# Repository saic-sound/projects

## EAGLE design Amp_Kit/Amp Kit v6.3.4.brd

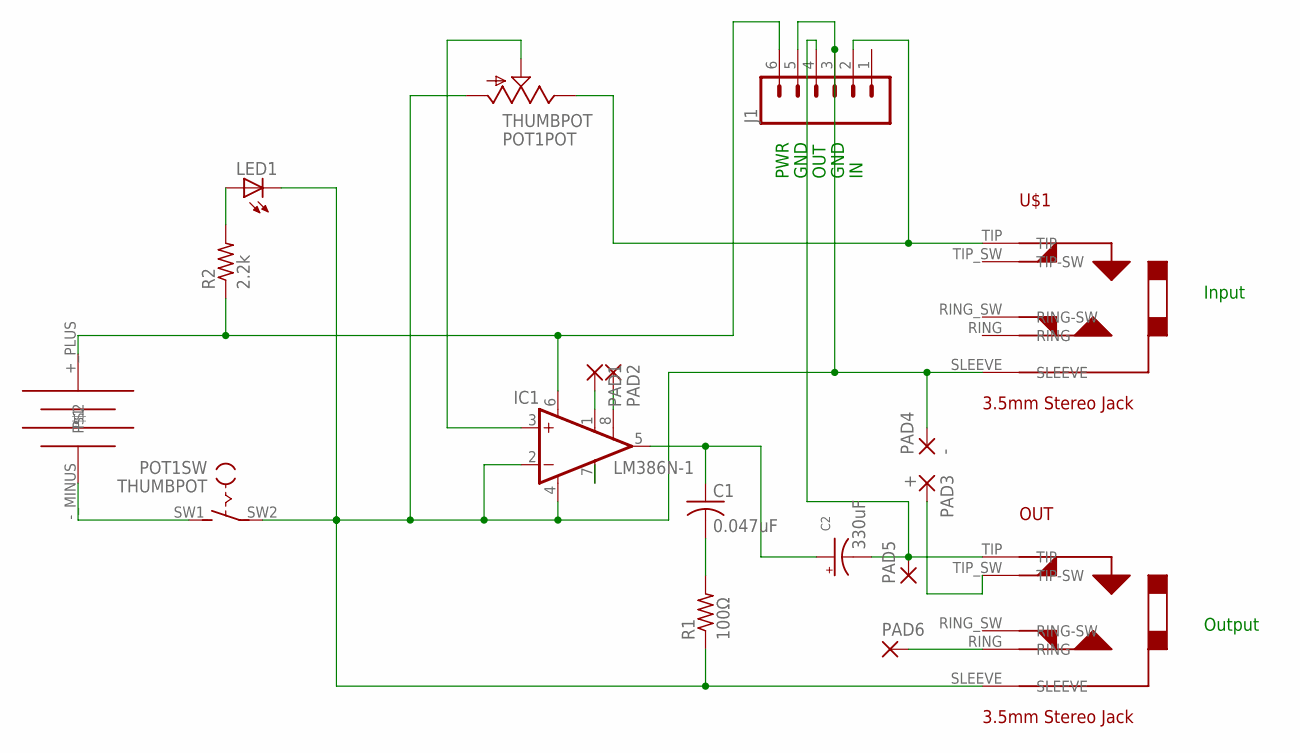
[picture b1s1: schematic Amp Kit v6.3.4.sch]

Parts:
C1: 0.047uF; C050-024X044
C2: 330uF; E1,8-4
IC1: LM386N-1; DIL08
J1: CONN_06NO_SILK_FEMALE_PTH; 1X06_NO_SILK
LED1: LED5MM
OUT: CUI_STEREO_JACK
PAD1, PAD2, PAD5, PAD6: SMD2; SMD1,27-2,54
PAD3: +; 4,16O1,6
PAD4: -; 4,16O1,6
POT1: THUMBPOT; THUMBWHEEL
R1: 100Ω; 0207/7
R2: 2.2k; 0207/7
U$1: CUI_STEREO_JACK
U$2: 9V_BATCLIP_AMP2

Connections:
unnamed: IC1.2 (-IN), IC1.4 (GND), J1.3, J1.5, LED1.K (C), OUT.SLEEVE, PAD4.1, POT1.1 (A), POT1.SW2, R1.1, U$1.SLEEVE
unnamed: OUT.TIP_SW (TIP-SW), PAD3.1
unnamed: C1.1, C2.+, IC1.5 (OUT)
unnamed: IC1.3 (+IN), POT1.2 (S)
unnamed: IC1.1 (GAIN), PAD1.1
unnamed: C2.-, J1.4, OUT.TIP, PAD5.1
unnamed: J1.2, POT1.3 (E), U$1.TIP
unnamed: LED1.A, R2.2
unnamed: POT1.SW1 (S), U$2.-_MINUS
unnamed: IC1.8 (GAIN), PAD2.1
unnamed: C1.2, R1.2
unnamed: OUT.RING, PAD6.1
unnamed: IC1.6 (VS), J1.6, R2.1, U$2.+_PLUS

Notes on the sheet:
Output
Input
PWR
GND
OUT

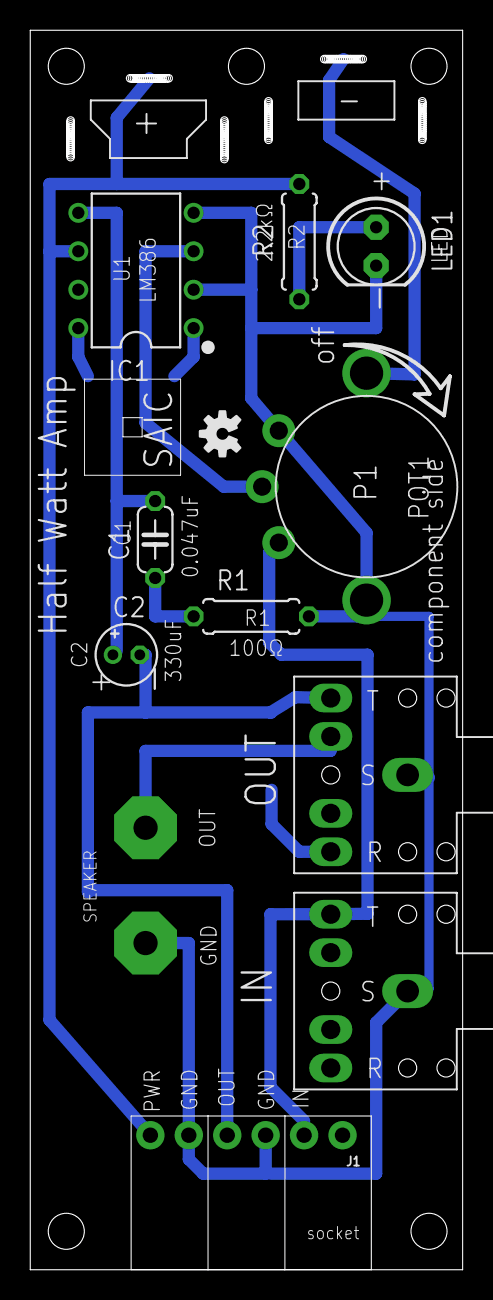
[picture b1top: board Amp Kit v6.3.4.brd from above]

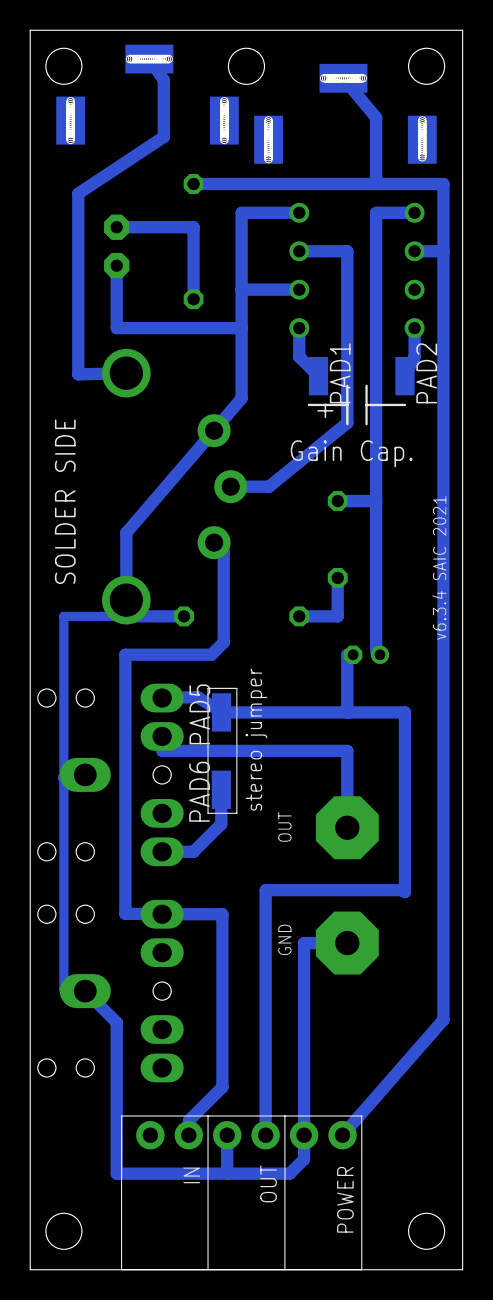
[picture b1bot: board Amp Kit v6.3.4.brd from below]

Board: 2 copper layers, 28.6 x 81.9 mm, 18 parts (4 on the bottom side), 13 nets.

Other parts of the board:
U$4: OSHW-LOGO-S

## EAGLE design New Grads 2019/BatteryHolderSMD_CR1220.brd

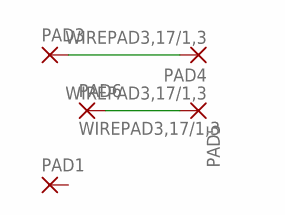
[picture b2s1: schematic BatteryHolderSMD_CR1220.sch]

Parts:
PAD1, PAD3: SMD5; SMD2,54-5,08
PAD4, PAD5, PAD6: WIREPAD3,17/1,3; 3,17/1,3

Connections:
unnamed: PAD3.1, PAD4.1
unnamed: PAD5.1, PAD6.1

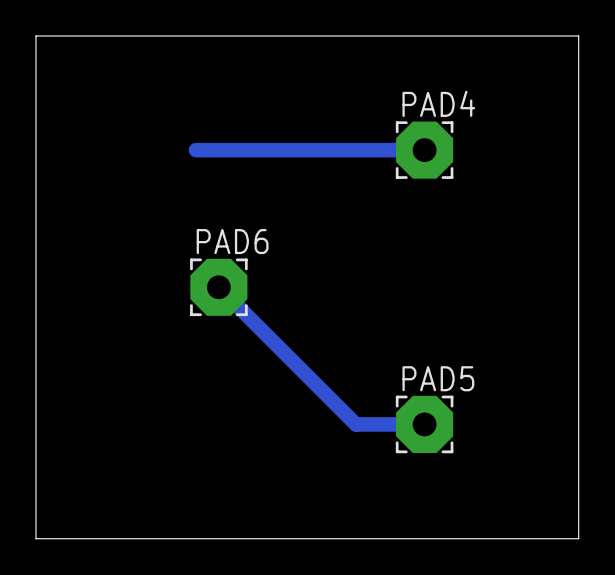
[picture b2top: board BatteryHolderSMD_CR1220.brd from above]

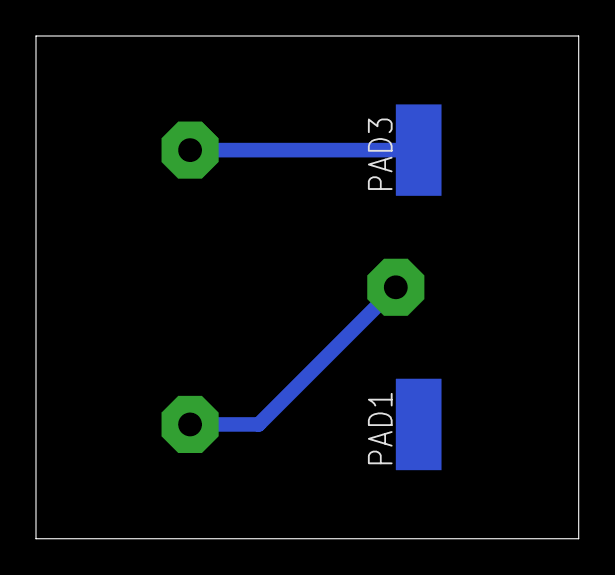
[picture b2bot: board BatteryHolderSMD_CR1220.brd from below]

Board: 2 copper layers, 30.1 x 27.9 mm, 5 parts (2 on the bottom side), 2 nets.

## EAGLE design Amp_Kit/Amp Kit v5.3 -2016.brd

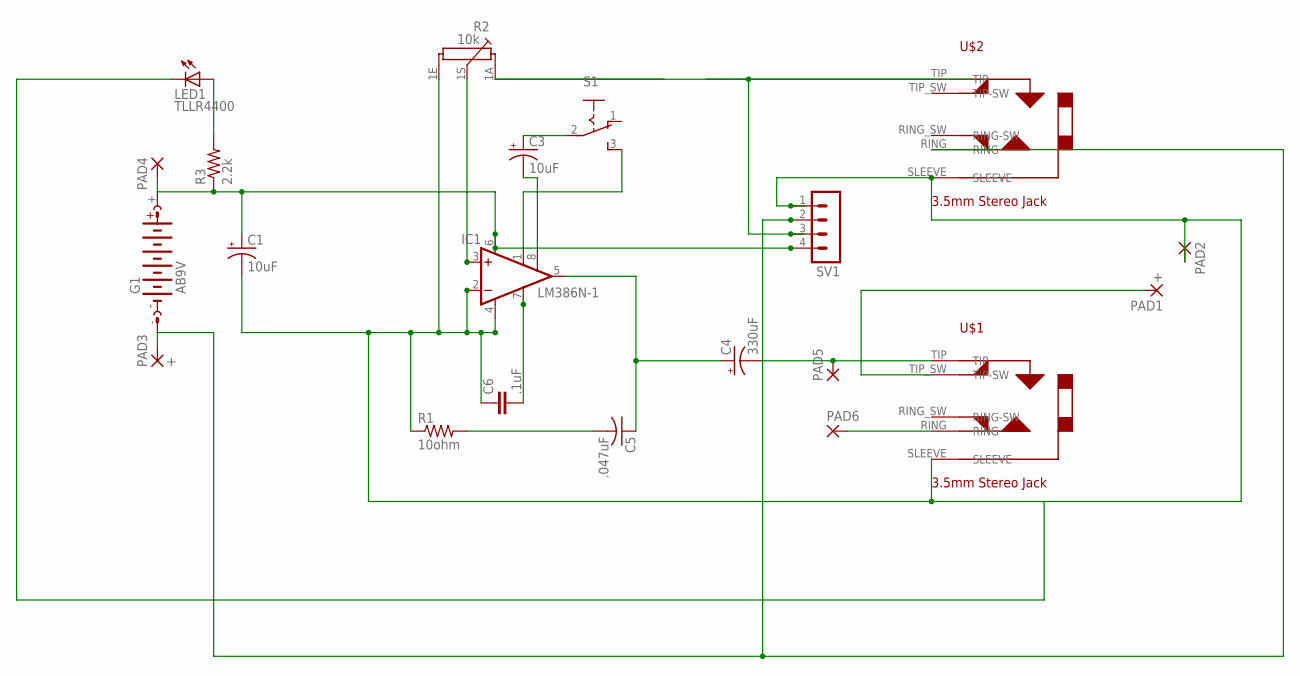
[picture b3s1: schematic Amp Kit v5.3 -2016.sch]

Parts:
C1, C3: 10uF; E2-5
C4: 330uF; E3,5-8
C5: .047uF; C050-025X075
C6: .1uF; C050-035X075
G1: AB9V
IC1: LM386N-1; DIL08
LED1: TLLR4400; LED3MM
PAD1, PAD3: +; 3,81/1,4
PAD2, PAD4: 3,81/1,4
PAD5, PAD6: SMD2; SMD1,27-2,54
R1: 10ohm; 0207/7
R2: 10k; PC16S
R3: 2.2k; 0207/7
S1: 255SB
SV1: MA04-1
U$1, U$2: PICAXE_STEREOJACKSOCKET

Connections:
unnamed: C5.2, R1.2
unnamed: R2.1A, SV1.3, U$2.TIP
unnamed: C4.+, C5.1, IC1.5 (OUT)
unnamed: IC1.3 (+IN), R2.1S
unnamed: C1.+, G1.+, IC1.6 (VS), PAD4.1, R3.1, SV1.4
unnamed: C4.-, PAD5.1, U$1.TIP
unnamed: C6.2, IC1.7 (BYPASS)
unnamed: C3.+, S1.2
unnamed: LED1.A, R3.2
unnamed: IC1.1 (GAIN), S1.3 (S)
unnamed: C1.-, C6.1, IC1.2 (-IN), IC1.4 (GND), LED1.K (C), PAD2.1, R1.1, R2.1E, SV1.1, U$1.SLEEVE, U$2.SLEEVE
unnamed: G1.-, PAD3.1, SV1.2, U$2.RING
unnamed: PAD6.1, U$1.RING
unnamed: C3.-, IC1.8 (GAIN)
unnamed: PAD1.1, U$1.TIP_SW (TIP-SW)

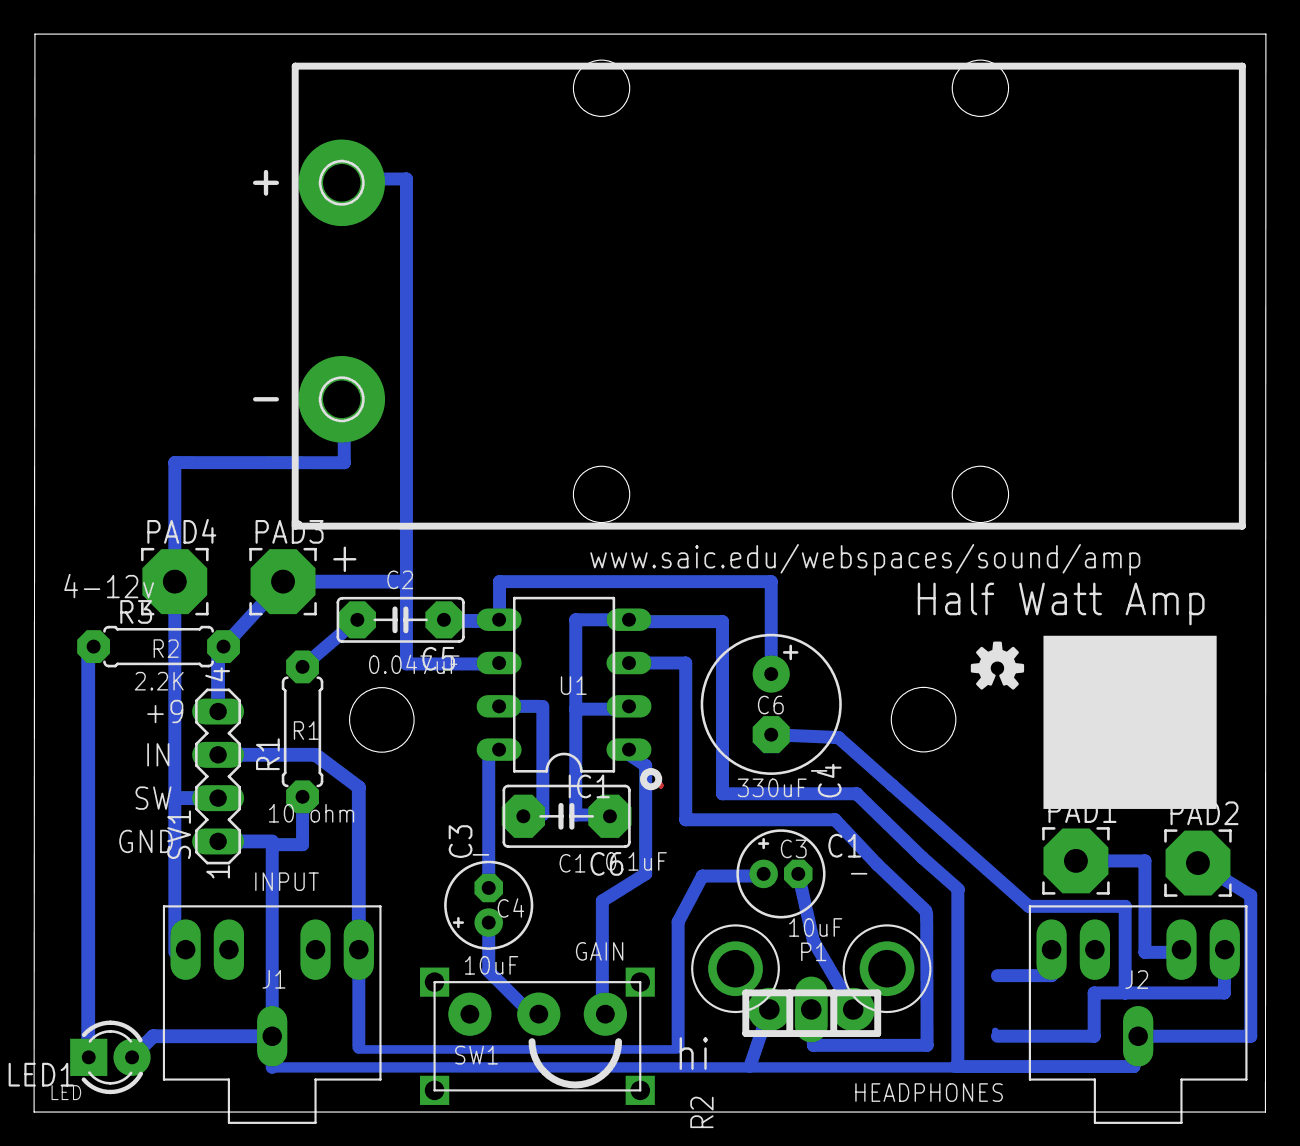
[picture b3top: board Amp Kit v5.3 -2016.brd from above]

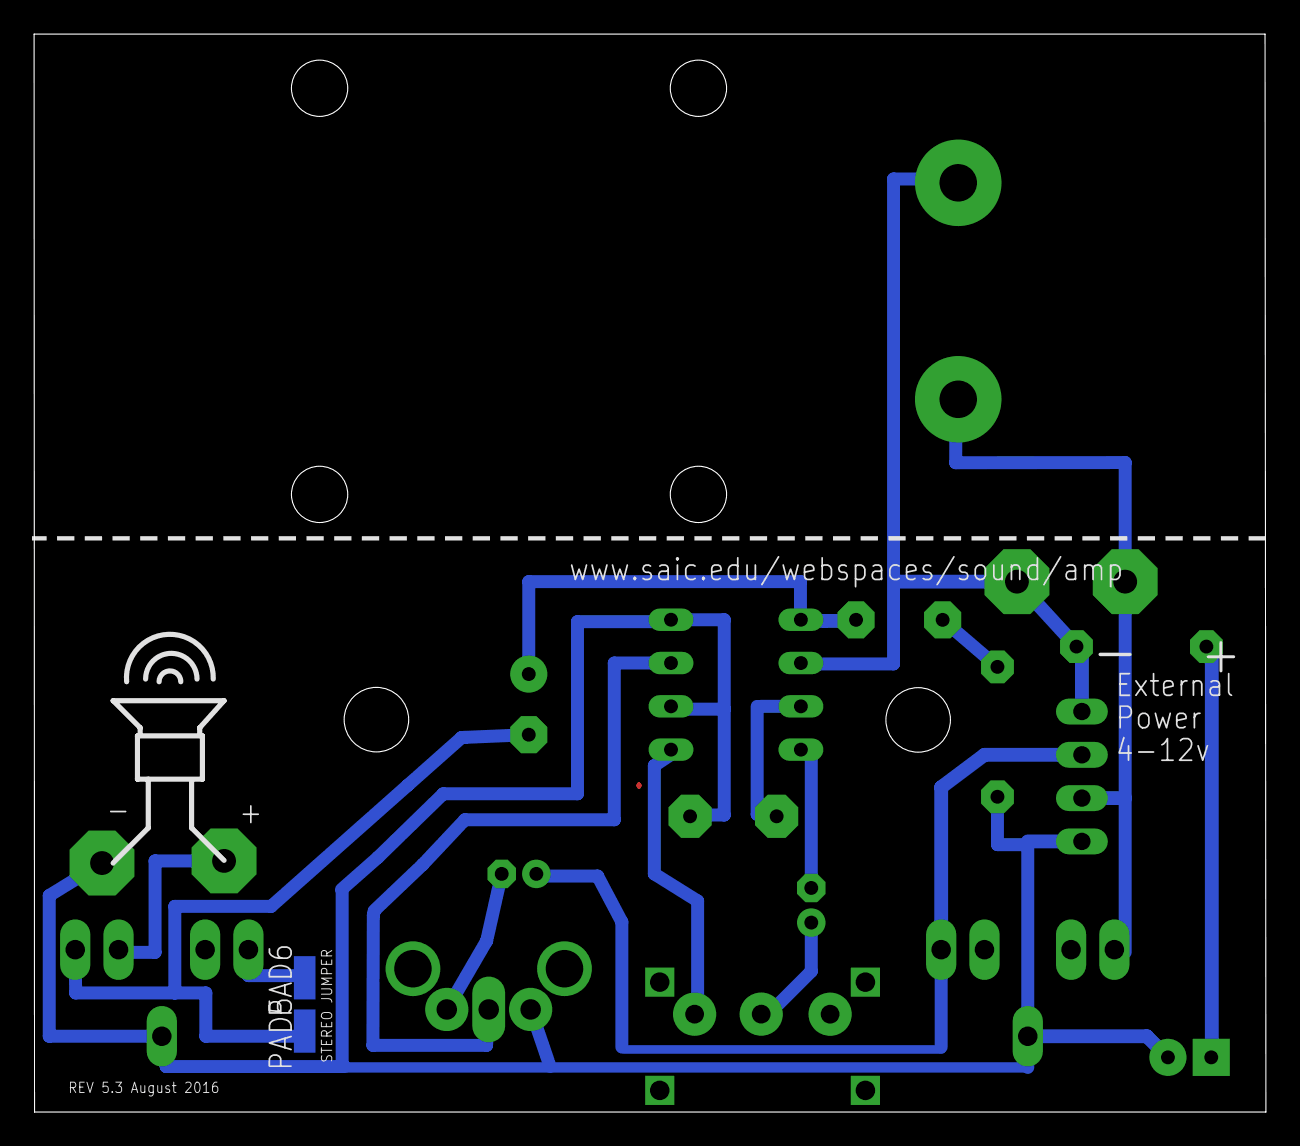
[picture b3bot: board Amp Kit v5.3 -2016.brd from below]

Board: 2 copper layers, 72.3 x 63.2 mm, 22 parts (2 on the bottom side), 15 nets.

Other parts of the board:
U$3: OSHW-LOGO-S

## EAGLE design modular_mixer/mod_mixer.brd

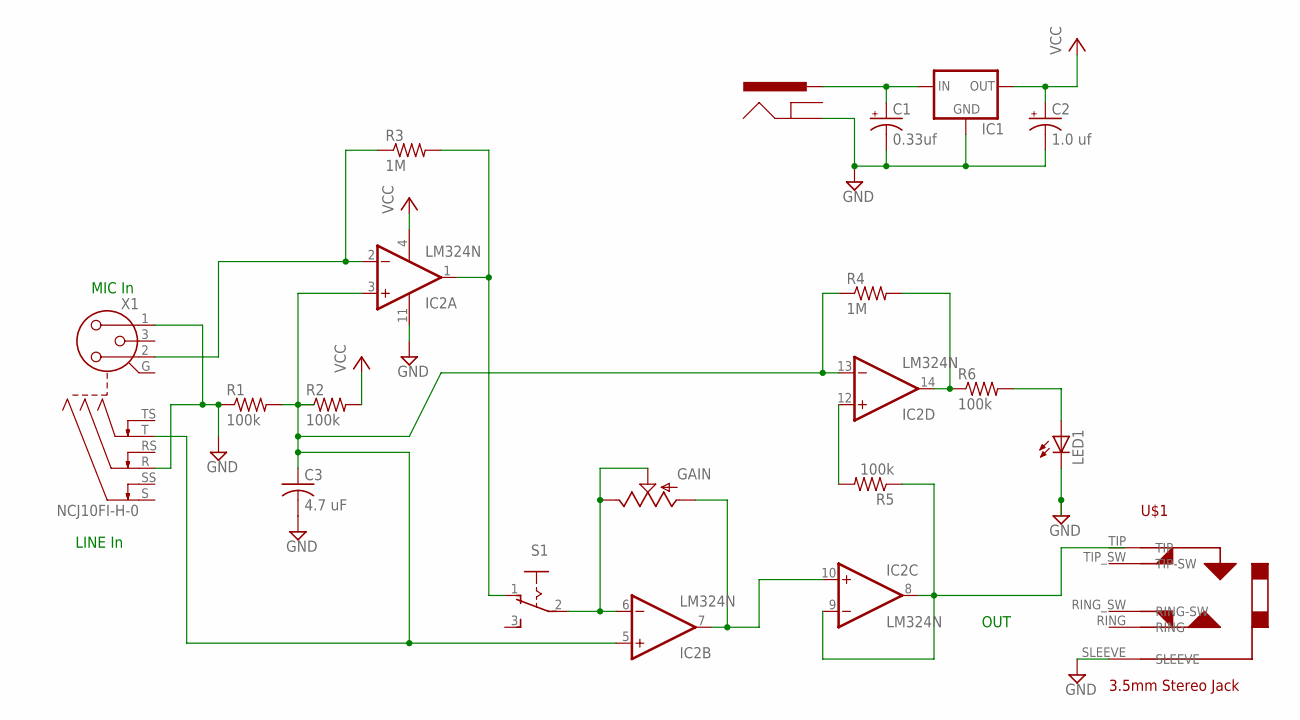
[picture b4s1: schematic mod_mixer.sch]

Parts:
C1: 0.33uf; E2,5-6
C2: 1.0 uf; E2,5-6
C3: 4.7 uF; C050-030X075
GAIN: POT; ALPS_POT
IC1: V_REG_78XXSIDE; 78XXL
IC2: LM324N; DIL14
J1: POWER_JACKSLT; POWER_JACK_SLOT
LED1: LED3MM
R1, R2, R5, R6: 100k; 0207/10
R3, R4: 1M; 0207/10
S1: 255SB
U$1: PICAXE_STEREOJACKSOCKET
X1: NCJ10FI-H-0

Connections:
GND: C1.-, C2.-, C3.2, IC1.GND, IC2.11 (V-), J1.GND@2 (GND), LED1.K (C), R1.1, U$1.SLEEVE, X1.1, X1.R
unnamed: C3.1, IC2.3 (+IN), IC2.5 (+IN), IC2.13 (-IN), R1.2, R2.1, R4.1, X1.T
unnamed: C1.+, IC1.IN, J1.PWR
unnamed: GAIN.P$3 (A), IC2.7 (OUT), IC2.10 (+IN)
unnamed: IC2.2 (-IN), R3.1, X1.2
unnamed: GAIN.P$1 (E), GAIN.P$2 (S), IC2.6 (-IN), S1.2
unnamed: IC2.8 (OUT), IC2.9 (-IN), R5.1
unnamed: IC2.1 (OUT), R3.2, S1.1 (O)
unnamed: IC2.12 (+IN), R5.2
unnamed: IC2.14 (OUT), R4.2, R6.1
unnamed: LED1.A, R6.2
VCC: C2.+, IC1.OUT, IC2.4 (V+), R2.2

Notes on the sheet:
MIC In
LINE In
OUT

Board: 2 copper layers, 17 parts (0 on the bottom side), 12 nets, no tracks yet.

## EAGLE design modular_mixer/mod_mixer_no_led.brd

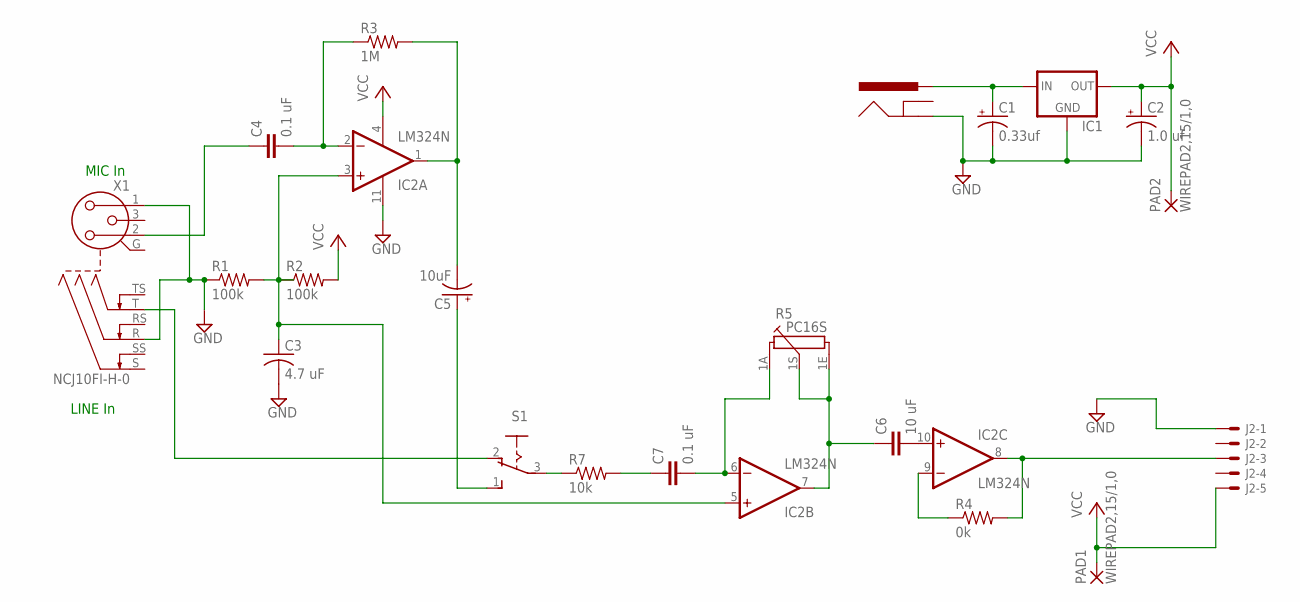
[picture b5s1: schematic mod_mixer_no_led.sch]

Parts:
C1: 0.33uf; E2,5-6
C2: 1.0 uf; E2,5-6
C3: 4.7 uF; C050-030X075
C4, C7: 0.1 uF; C5B2.5
C5: 10uF; E2,5-7
C6: 10 uF; C5B2.5
IC1: V_REG_78XXSIDE; 78XXL
IC2: LM324N; DIL14
J1: POWER_JACKSLT; POWER_JACK_SLOT
J2: CON-50-EDGE; CARDEDGE-50
PAD1, PAD2: WIREPAD2,15/1,0; 2,15/1,0
R1, R2: 100k; 0207/10
R3: 1M; 0207/10
R4: 0k; 0207/10
R5: PC16S
R7: 10k; 0207/10
S1: 255SB
X1: NCJ10FI-H-0

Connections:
GND: C1.-, C2.-, C3.2, IC1.GND, IC2.11 (V-), J1.GND@2 (GND), J2.1, R1.1, X1.1, X1.R
unnamed: C3.1, IC2.3 (+IN), IC2.5 (+IN), R1.2, R2.1
unnamed: C1.+, IC1.IN, J1.PWR
unnamed: C7.1, R7.2
unnamed: C4.2, IC2.2 (-IN), R3.1
unnamed: C7.2, IC2.6 (-IN), R5.1A
unnamed: C5.-, IC2.1 (OUT), R3.2
unnamed: R7.1, S1.3
unnamed: S1.2 (O), X1.T
unnamed: C4.1, X1.2
unnamed: C5.+, S1.1 (S)
unnamed: C6.2, IC2.10 (+IN)
unnamed: IC2.9 (-IN), R4.1
unnamed: IC2.8 (OUT), J2.3, R4.2
unnamed: C6.1, IC2.7 (OUT), R5.1E, R5.1S
VCC: C2.+, IC1.OUT, IC2.4 (V+), J2.5, PAD1.1, PAD2.1, R2.2

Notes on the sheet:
MIC In
LINE In

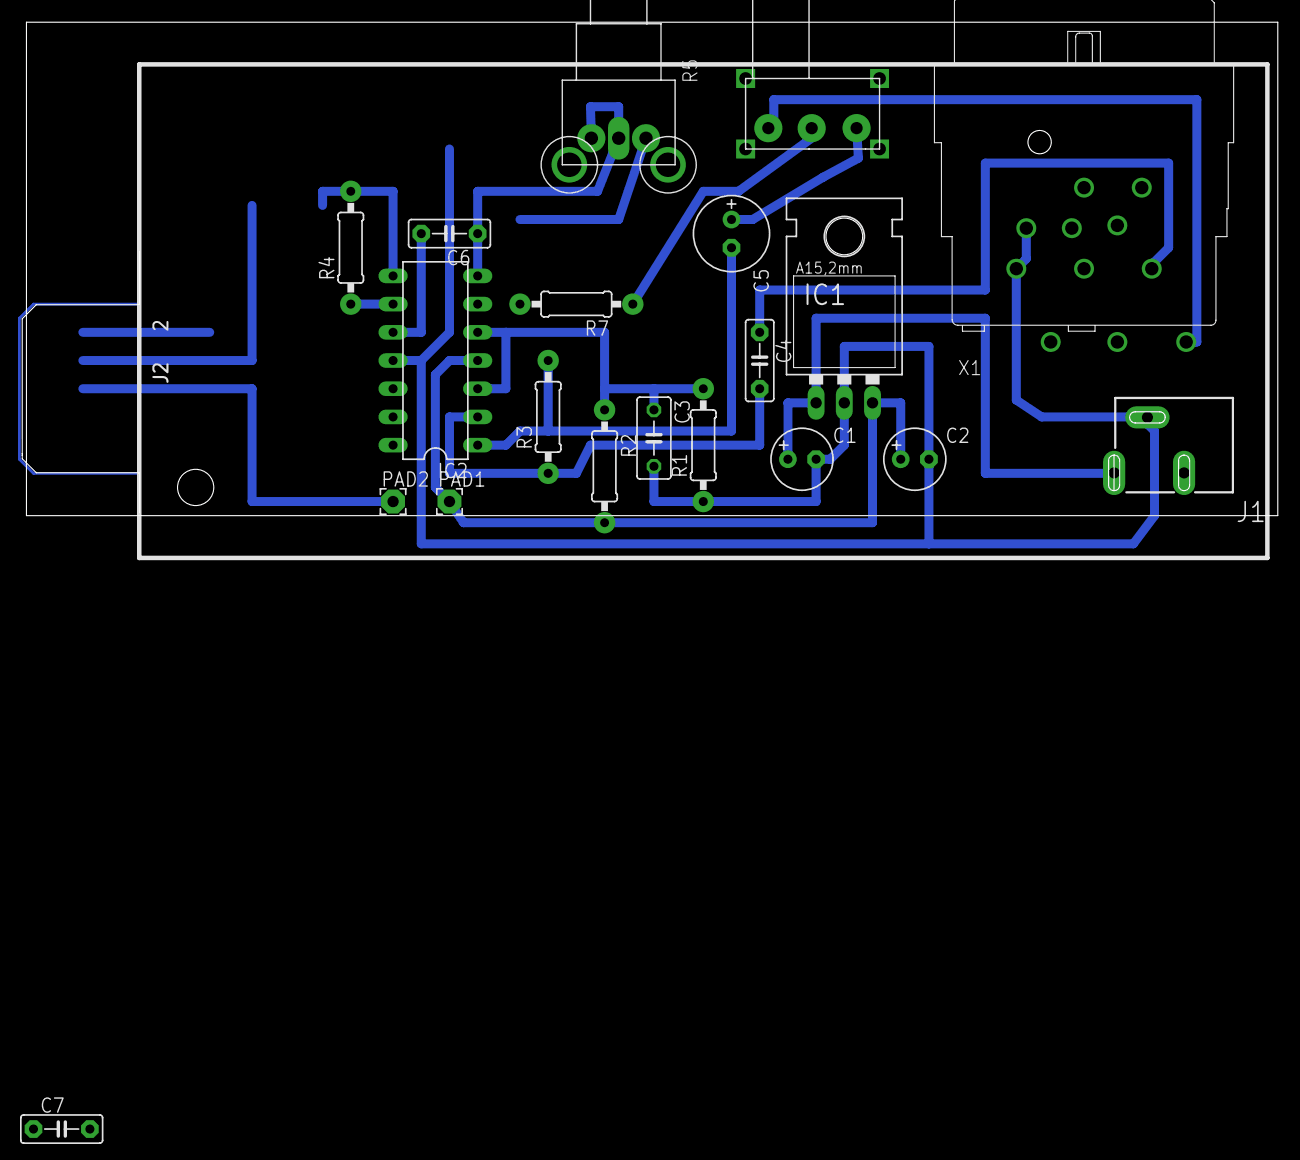
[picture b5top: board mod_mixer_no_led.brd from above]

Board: 2 copper layers, 112.7 x 44.4 mm, 21 parts (0 on the bottom side), 16 nets.

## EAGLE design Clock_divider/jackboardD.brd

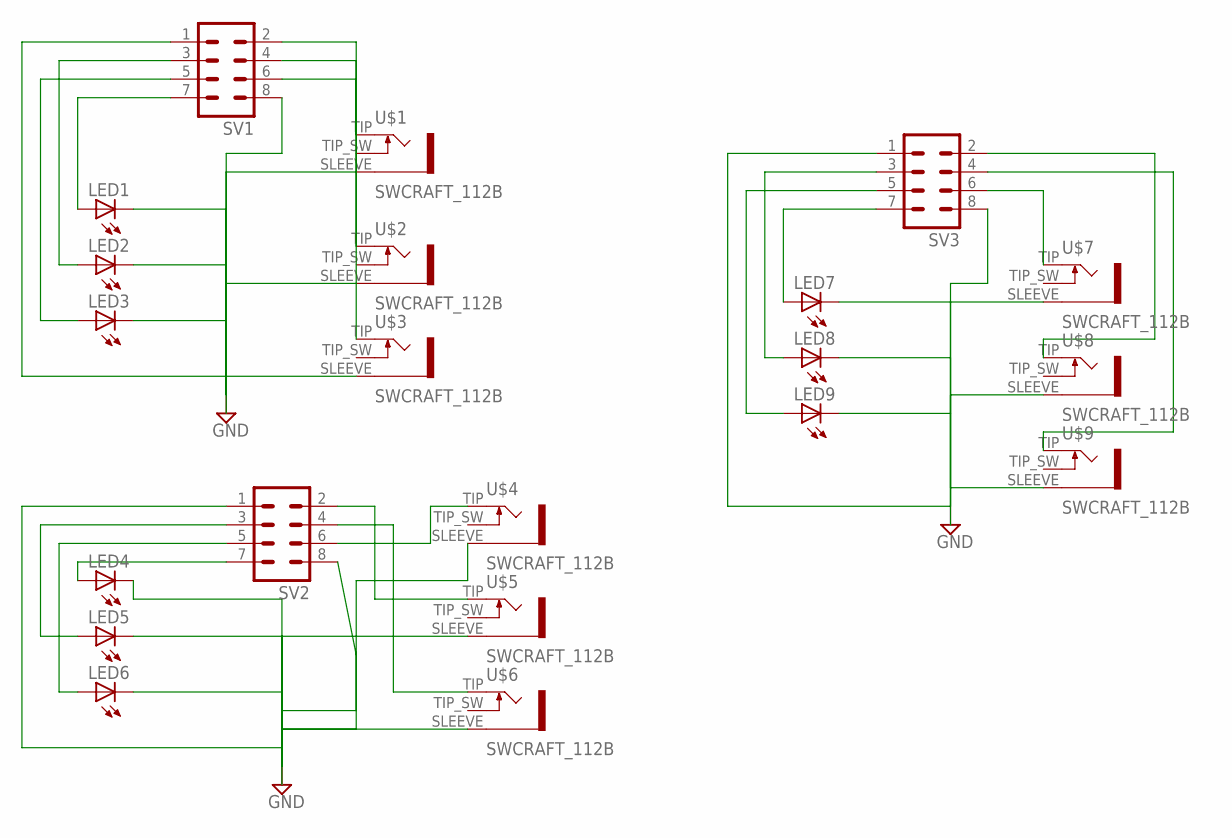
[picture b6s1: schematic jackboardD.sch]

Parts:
LED1, LED2, LED3, LED4, LED5, LED6, LED7, LED8, LED9: LED5MM
SV1, SV2, SV3: MA04-2
U$1, U$2, U$3, U$4, U$5, U$6, U$7, U$8, U$9: SWCRAFT_112B; SWCRAFT_112_SLOTS

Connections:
GND: LED2.K (C), LED5.K (C), LED7.K (C), LED8.K (C), SV2.1, SV2.8, SV3.1, U$1.SLEEVE (5), U$5.SLEEVE (5), U$6.SLEEVE (5), U$7.SLEEVE (5)
unnamed: LED1.A, SV1.7
unnamed: LED2.A, SV1.3
unnamed: LED3.A, SV1.5
unnamed: SV1.6, U$1.TIP (3)
unnamed: SV1.2, U$2.TIP (3)
unnamed: LED4.K (C), LED6.K (C), U$4.SLEEVE (5)
unnamed: SV1.4, U$3.TIP (3)
unnamed: LED1.K (C), LED3.K (C), SV1.1, SV1.8, U$2.SLEEVE (5), U$3.SLEEVE (5)
unnamed: LED6.A, SV2.5
unnamed: LED4.A, SV2.7
unnamed: LED5.A, SV2.3
unnamed: SV2.2, U$5.TIP (3)
unnamed: SV2.4, U$6.TIP (3)
unnamed: SV2.6, U$4.TIP (3)
unnamed: LED9.K (C), SV3.8, U$8.SLEEVE (5), U$9.SLEEVE (5)
unnamed: LED7.A, SV3.7
unnamed: LED9.A, SV3.5
unnamed: LED8.A, SV3.3
unnamed: SV3.2, U$8.TIP (3)
unnamed: SV3.4, U$9.TIP (3)
unnamed: SV3.6, U$7.TIP (3)

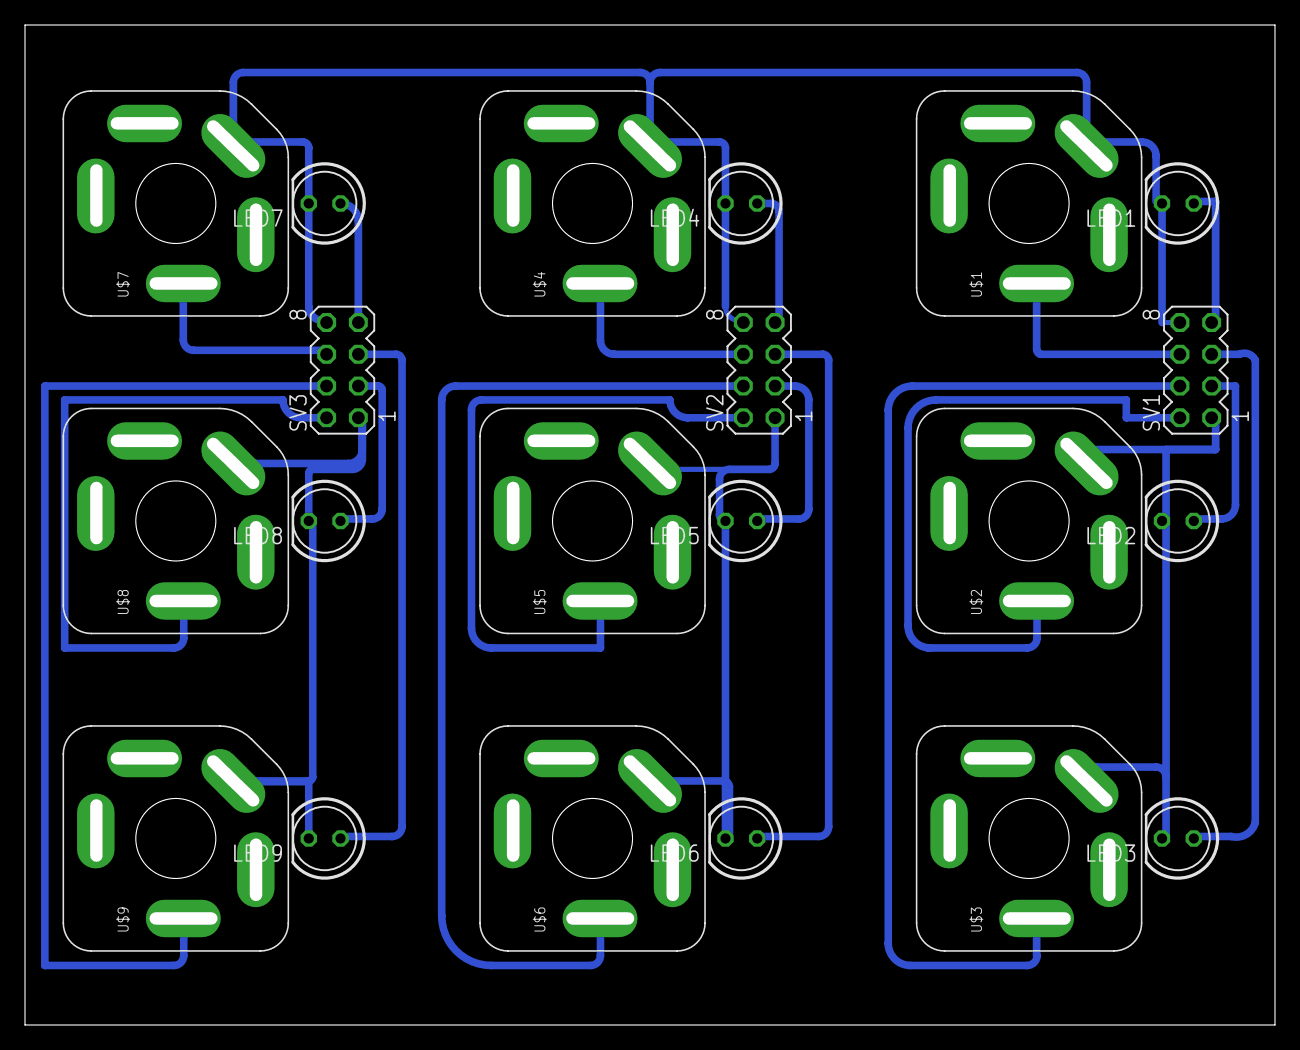
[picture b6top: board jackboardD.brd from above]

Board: 2 copper layers, 100.0 x 80.0 mm, 22 parts (0 on the bottom side), 22 nets.

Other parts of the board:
DRILEGEND: DRILEGEND

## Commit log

2017-02-10 first push of Emu files
2017-02-10 added Emu folder and mixer
2017-02-10 Please enter the commit message for your changes. Lines starting
2019-01-07 Added New Grads 2019 folder
    Added New Grads 2019 folder
2024-06-19 v6.3.4

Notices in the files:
parts and their libraries:
Particle-Devices: Licensing: Designed by Particle.
SparkFun-Connectors: Licensing: Creative Commons ShareAlike 4.0 International - https://creativecommons.org/licenses/by-sa/4.0
